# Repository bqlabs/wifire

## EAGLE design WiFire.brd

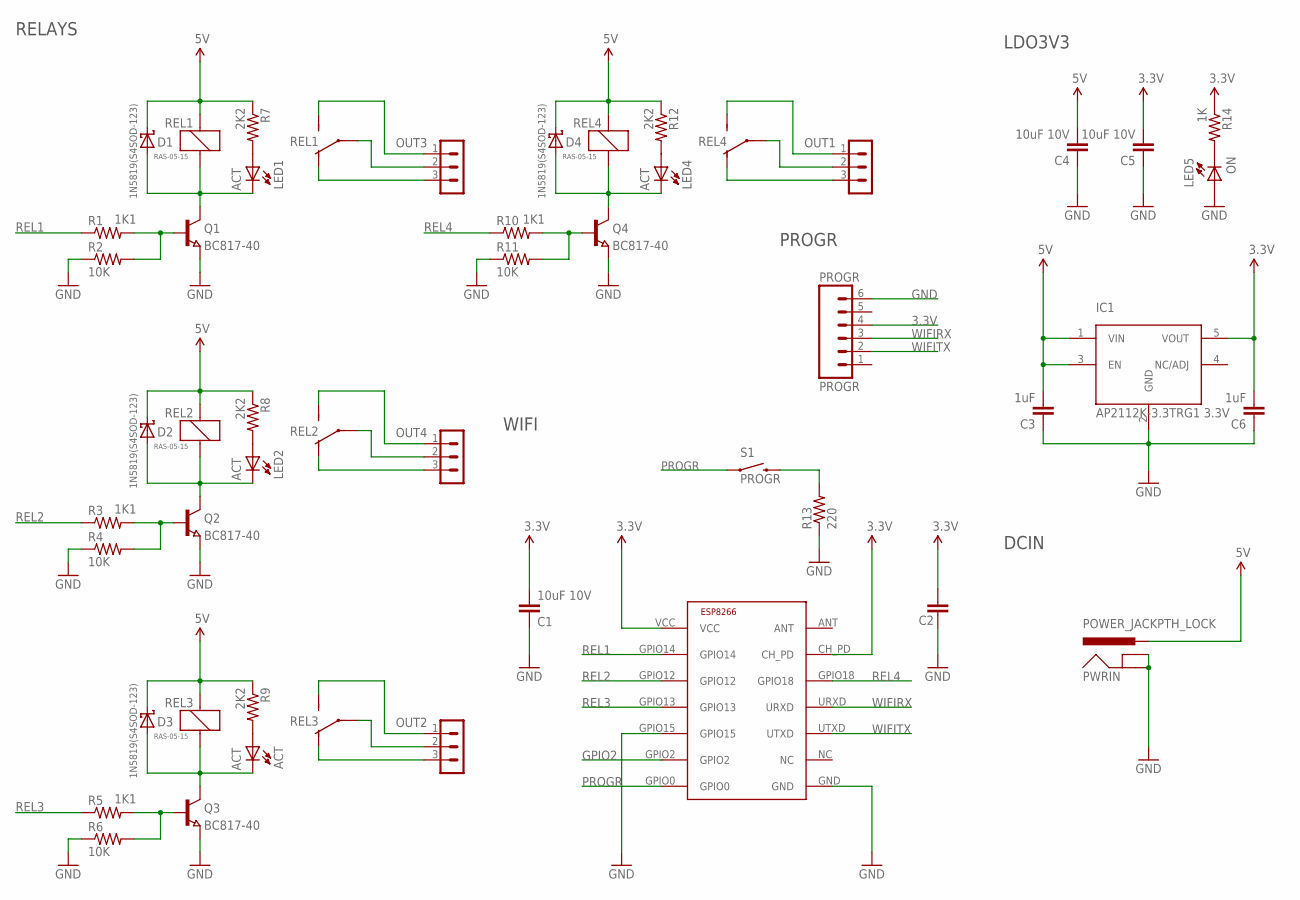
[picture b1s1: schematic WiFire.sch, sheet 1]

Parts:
ACT: ACT; LED-0603_L
C1, C4, C5: 10uF 10V; 0402-CAP
C2: 0.1uF; 0402-CAP
C3, C6: 1uF; 0402-CAP
D1, D2, D3, D4: 1N5819(S4SOD-123); SOD-123
IC1: AP2112K-3.3TRG1 3.3V; SOT23-5
LED1, LED2, LED4: ACT; LED-0603_L
LED5: ON; LED-0603_L
OUT1, OUT2, OUT3, OUT4: CON3-DG306-5.0_3P(TB3-5MM); DG306-5.0_3P
PROGR: PROGR; 1X06_SMD_MALE
PWRIN: POWER_JACKPTH_LOCK; POWER_JACK_PTH_LOCK
Q1, Q2, Q3, Q4: BC817-40; SOT23
R1, R3, R5, R10: 1K1; 0402-RES
R2, R4, R6, R11: 10K; 0402-RES
R7, R8, R9, R12: 2K2; 0402-RES
R13: 220; 0402-RES
R14: 1K; 0402-RES
REL1, REL2, REL3, REL4: RAS-05-15; H200-FAT
S1: PROGR; TACTILE-PTH-SIDEEZ
U1: ESP8266; ESP-03

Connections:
3.3V: C1.2, C2.2, C5.2, C6.2, IC1.5 (VOUT), PROGR.4, R14.1, U1.CH_PD, U1.VCC
5V: C3.2, C4.2, D1.C, D2.C, D3.C, D4.C, IC1.1 (VIN), IC1.3 (EN), PWRIN.PWR, R7.1, R8.1, R9.1, R12.1, REL1.1, REL2.1, REL3.1, REL4.1; also elsewhere on the board
COM: OUT3.2, REL1.P
COM1: OUT4.2, REL2.P
COM2: OUT2.2, REL3.P
COM3: OUT1.2, REL4.P
GND: C1.1, C2.1, C3.1, C4.1, C5.1, C6.1, IC1.2 (GND), LED5.A, PROGR.6, PWRIN.GND, PWRIN.GNDBREAK, Q1.2 (E), Q2.2 (E), Q3.2 (E), Q4.2 (E), R2.1, R4.1, R6.1, R11.1, R13.1, U1.GND, U1.GPIO15; also elsewhere on the board
GPIO2: U1.GPIO2
unnamed: LED1.A, R7.2
unnamed: Q2.1 (B), R3.2, R4.2
unnamed: D2.A, LED2.C, Q2.3 (C), REL2.2
unnamed: LED2.A, R8.2
unnamed: Q3.1 (B), R5.2, R6.2
unnamed: ACT.C, D3.A, Q3.3 (C), REL3.2
unnamed: ACT.A, R9.2
unnamed: Q4.1 (B), R10.2, R11.2
unnamed: D4.A, LED4.C, Q4.3 (C), REL4.2
unnamed: LED4.A, R12.2
unnamed: R13.2, S1.2
unnamed: LED5.C, R14.2
unnamed: Q1.1 (B), R1.2, R2.2
unnamed: D1.A, LED1.C, Q1.3 (C), REL1.2
NC: OUT3.3, REL1.O
NC1: OUT4.3, REL2.O
NC2: OUT2.3, REL3.O
NC3: OUT1.3, REL4.O
NO: OUT3.1, REL1.S
NO1: OUT4.1, REL2.S
NO2: OUT2.1, REL3.S
NO3: OUT1.1, REL4.S
PROGR: S1.1, U1.GPIO0
REL1: R1.1, U1.GPIO14; also elsewhere on the board
REL2: R3.1, U1.GPIO12; also elsewhere on the board
REL3: R5.1, U1.GPIO13; also elsewhere on the board
REL4: R10.1, U1.GPIO18
WIFIRX: PROGR.3, U1.URXD
WIFITX: PROGR.2, U1.UTXD

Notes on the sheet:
WIFI
RELAYS
LDO3V3
PROGR
DCIN

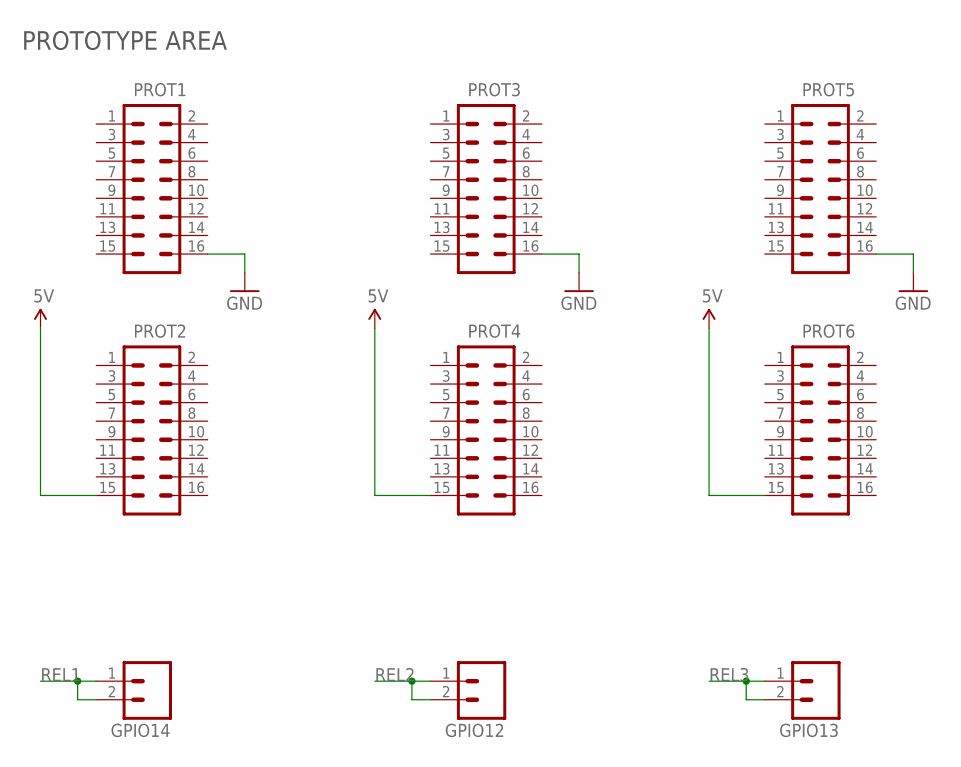
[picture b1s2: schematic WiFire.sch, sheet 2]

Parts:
GPIO12, GPIO13, GPIO14: M02PTH; 1X02
PROT1, PROT2, PROT3, PROT4, PROT5, PROT6: M08X2; 2X8

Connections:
5V: PROT2.15, PROT4.15, PROT6.15; also elsewhere on the board
GND: PROT1.16, PROT3.16, PROT5.16; also elsewhere on the board
REL1: GPIO14.1, GPIO14.2; also elsewhere on the board
REL2: GPIO12.1, GPIO12.2; also elsewhere on the board
REL3: GPIO13.1, GPIO13.2; also elsewhere on the board

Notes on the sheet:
PROTOTYPE AREA

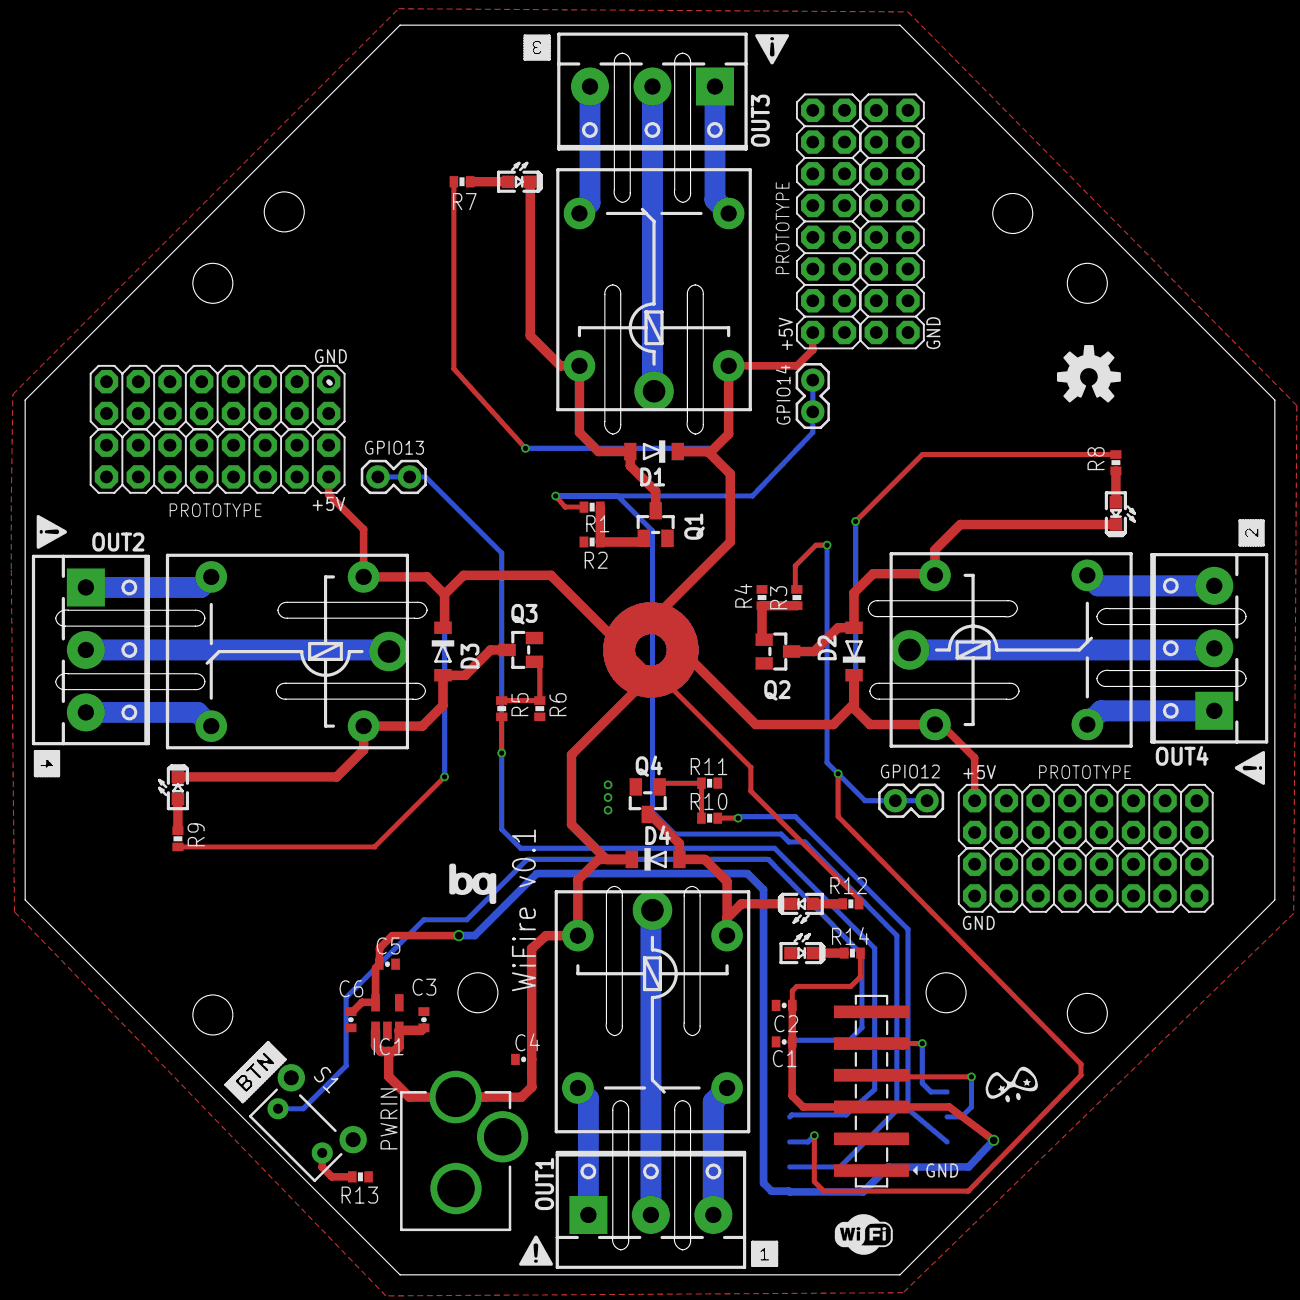
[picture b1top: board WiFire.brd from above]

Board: 2 copper layers, 100.0 x 100.0 mm, 68 parts (1 on the bottom side), 36 nets.

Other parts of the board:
U$1: BQ_LOGO_MEDIUM
U$2: S_1
U$3: S_2
U$4: S_3
U$5: S_4
U$6, U$10, U$11, U$12: S_ATTENTION
U$7: OSHW-LOGO-M
U$8: S_WIFI
U$9: S_BTN
U$13: PIGHIXXX_LOGO

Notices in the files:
parts and their libraries:
SparkFun-Passives: Licensing: Creative Commons ShareAlike 4.0 International - https://creativecommons.org/licenses/by-sa/4.0
